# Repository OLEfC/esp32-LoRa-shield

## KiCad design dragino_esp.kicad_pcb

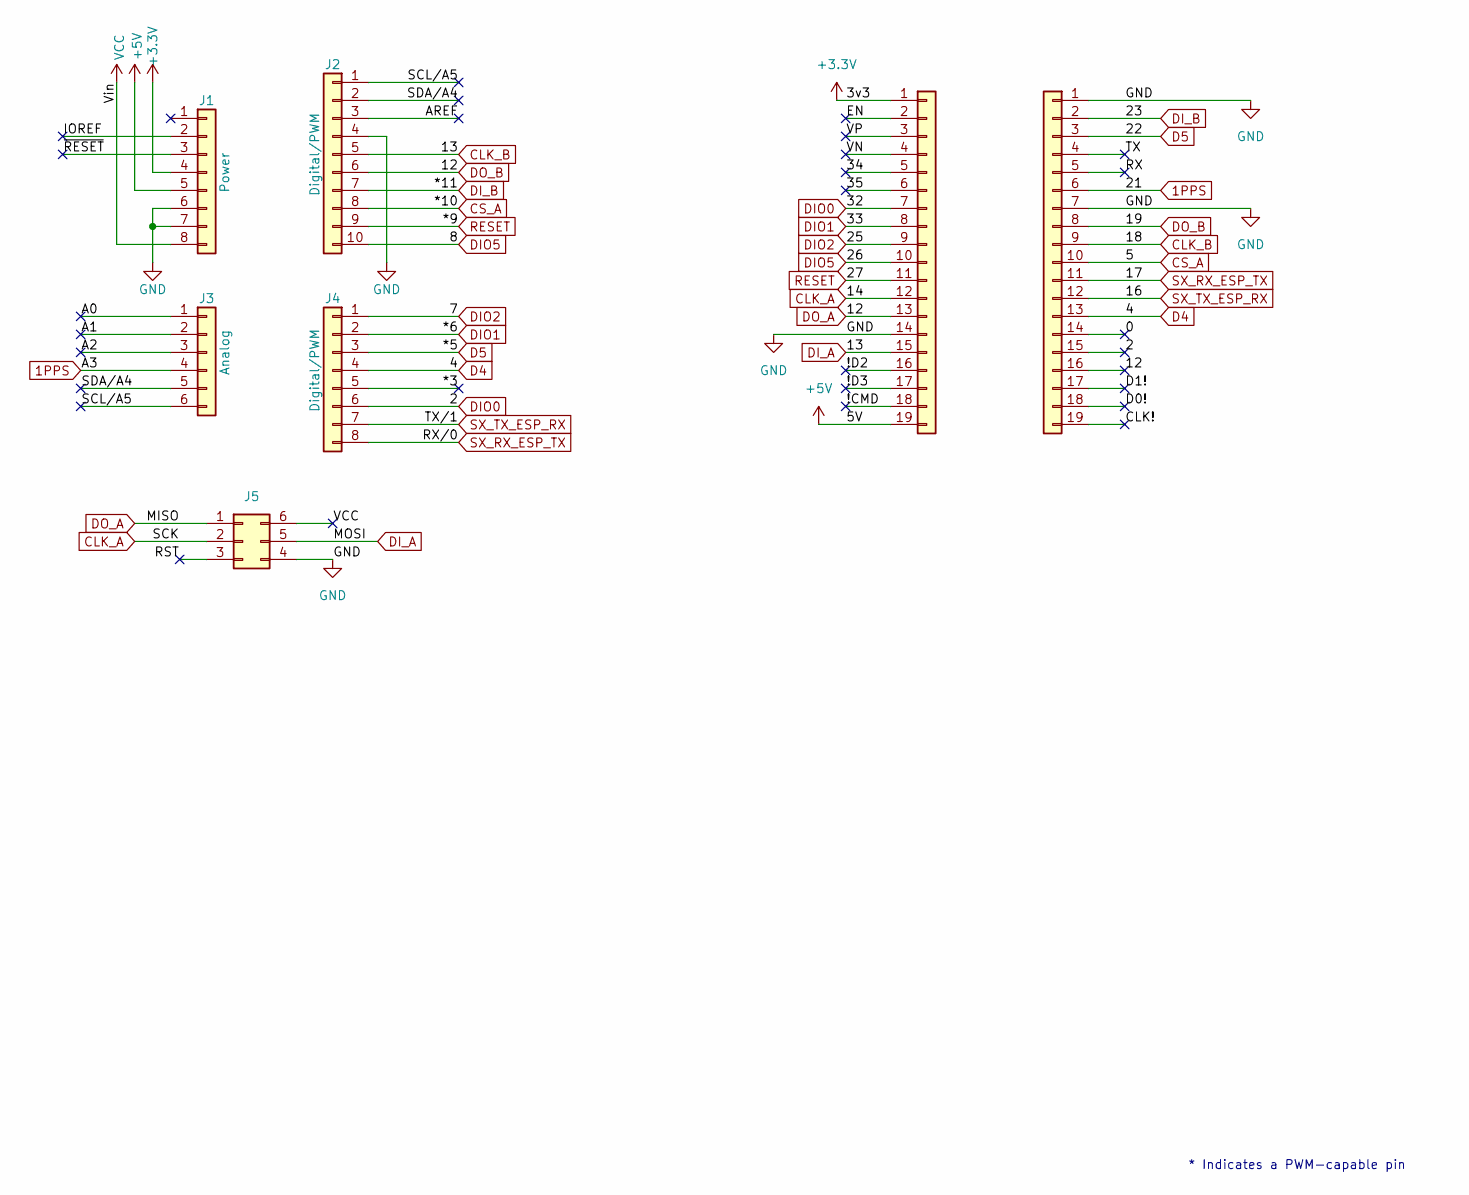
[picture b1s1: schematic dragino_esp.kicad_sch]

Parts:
J1: Power; PinSocket_1x08_P2.54mm_Vertical
J2: Digital/PWM; PinSocket_1x10_P2.54mm_Vertical
J3: Analog; PinSocket_1x06_P2.54mm_Vertical
J4: Digital/PWM; PinSocket_1x08_P2.54mm_Vertical
J5: Conn_02x03_Counter_Clockwise; PinHeader_2x03_P2.54mm_Vertical
J6, J7: Conn_01x19; PinSocket_1x19_P2.54mm_Vertical

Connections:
1PPS: J3.4, J7.6
+3.3V: J1.4, J6.1
+5V: J1.5, J6.19
/0: J7.14
/34: J6.5
/35: J6.6
/!CMD: J6.18
/!D2: J6.16
/!D3: J6.17
/*3: J4.5
/A0: J3.1
/A1: J3.2
/A2: J3.3
/AREF: J2.3
/CLK!: J7.19
/D0!: J7.18
/D1!: J7.17
/EN: J6.2
/IOREF: J1.2
/RST: J5.3
/RX: J7.5
/SCL/A5: J2.1, J3.6
/SDA/A4: J2.2, J3.5
/TX: J7.4
/VN: J6.4
/VP: J6.3
/~RESET: J1.3
CLK_A: J5.2, J6.12
CLK_B: J2.5, J5.5, J6.15, J7.9
CS_A: J2.8, J7.10
D4: J4.4, J7.13
D5: J4.3, J7.3
DIO0: J4.6, J6.7, J7.15
DIO1: J4.2, J6.8
DIO2: J4.1, J6.9
DIO5: J2.10, J6.10
DI_B: J2.7, J7.2
DO_A: J2.6, J5.1, J6.13, J7.8, J7.16
GND: J1.6, J1.7, J2.4, J5.4, J6.14, J7.1, J7.7
RESET: J2.9, J6.11
SX_RX_ESP_TX: J4.8, J7.11
SX_TX_ESP_RX: J4.7, J7.12
VCC: J1.8, J5.6

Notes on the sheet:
* Indicates a PWM-capable pin

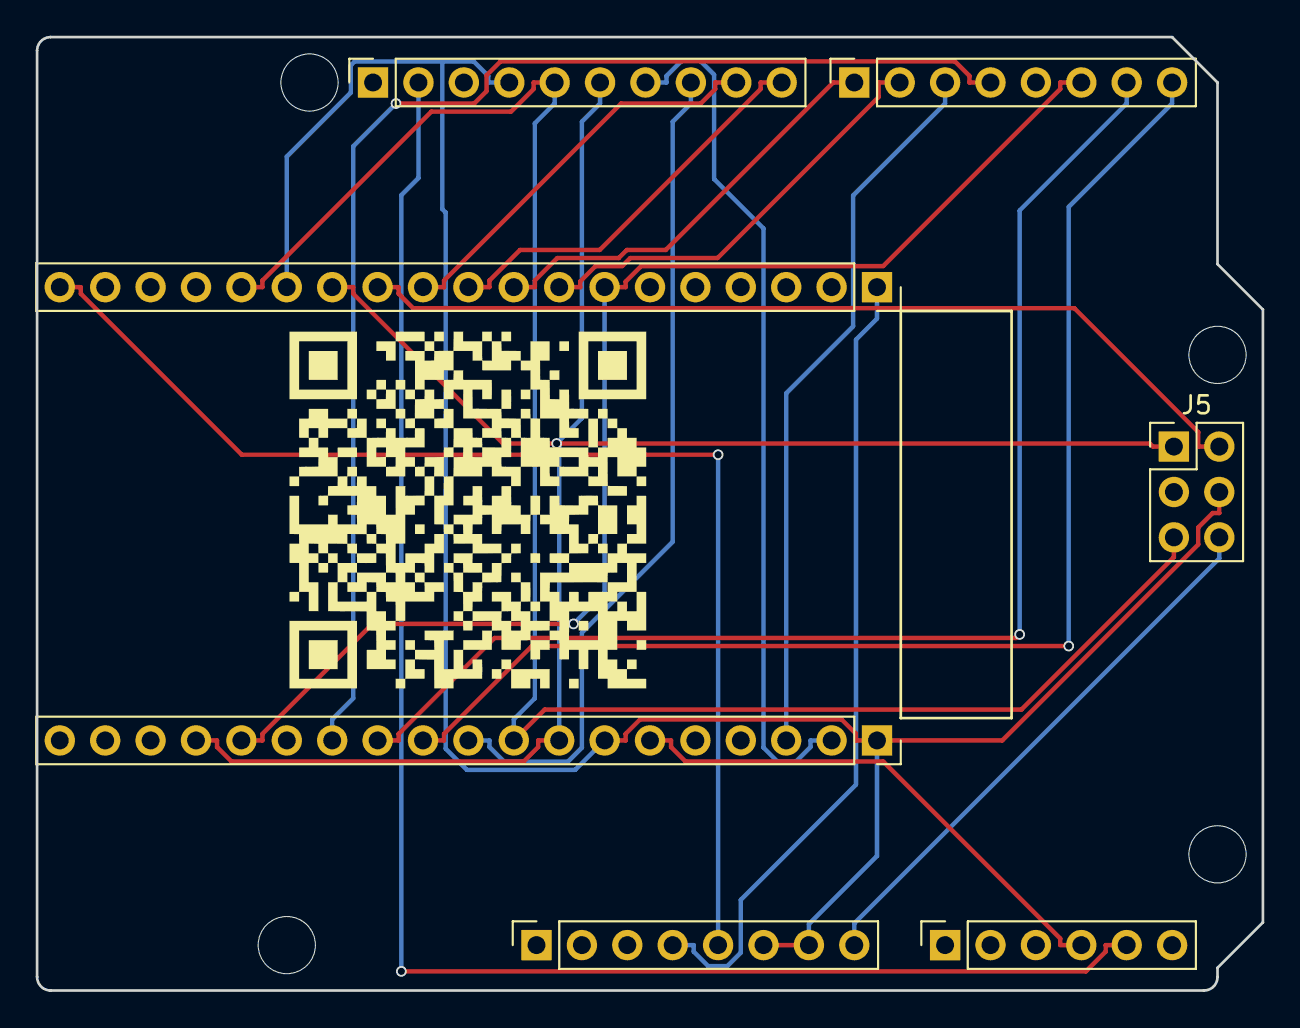
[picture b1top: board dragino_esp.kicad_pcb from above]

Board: 2 copper layers, 68.6 x 53.3 mm, 11 parts (0 on the bottom side), 21 nets.

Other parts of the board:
MH1, MH2, MH3, MH4: MountingHole_3.2mm
